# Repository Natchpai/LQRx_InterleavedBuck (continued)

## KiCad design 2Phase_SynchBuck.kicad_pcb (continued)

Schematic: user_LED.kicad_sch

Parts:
C801, C802: 100n; C_0402_nomDensity; Manufacturer Part Number GRM155R71H104KE14D
LD801, LD804: Orange; LED_0603_1608Metric; Manufacturer Part Numbe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 LTST-C190KFKT
LD802: Green; LED_0603_1608Metric; Manufacturer Part Numbe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 LTST-C191TGKT
LD803: Red; LED_0603_1608Metric; Manufacturer Part Numbe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 LTST-C191KRKT
Q801, Q802, Q803, Q804: GS2N7002KW; SOT-323_SC-70; Manufacturer Part Number GS2N7002KW
R801, R804: 499; R_0402_nomDensity; Manufacturer Part Number RC0402FR-07499RL
R802, R803: 1k; R_0402_nomDensity; Manufacturer Part Number RC0402FR-071KL
R805, R806, R807, R808: 100R; R_0402_nomDensity; Manufacturer Part Number RC0402FR-07100RL
R809, R810, R811, R812: 100k; R_0402_nomDensity; Manufacturer Part Number RC0402FR-07100KL

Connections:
+3V3: C801.1, C802.1, R801.1, R802.1, R803.1, R804.1; also elsewhere on the board
/Top/MCU IOs/LED_FAULT: R807.1, R811.1; also elsewhere on the board
/Top/MCU IOs/LED_IDLE: R805.1, R809.1; also elsewhere on the board
/Top/MCU IOs/LED_RUN: R806.1, R810.1; also elsewhere on the board
/Top/MCU IOs/LED_USER1: R808.1, R812.1; also elsewhere on the board
/Top/User LEDs/FLT_G: Q803.1 (G), R807.2
/Top/User LEDs/IDLE_G: Q801.1 (G), R805.2
/Top/User LEDs/LED_FLT_A: LD803.2 (A), R803.2
/Top/User LEDs/LED_FLT_K: LD803.1 (K), Q803.3 (D)
/Top/User LEDs/LED_IDLE_A: LD801.2 (A), R801.2
/Top/User LEDs/LED_IDLE_K: LD801.1 (K), Q801.3 (D)
/Top/User LEDs/LED_RUN_A: LD802.2 (A), R802.2
/Top/User LEDs/LED_RUN_K: LD802.1 (K), Q802.3 (D)
/Top/User LEDs/LED_USER1_A: LD804.2 (A), R804.2
/Top/User LEDs/LED_USER1_K: LD804.1 (K), Q804.3 (D)
/Top/User LEDs/RUN_G: Q802.1 (G), R806.2
/Top/User LEDs/USER1_G: Q804.1 (G), R808.2
GND: C801.2, C802.2, Q801.2 (S), Q802.2 (S), Q803.2 (S), Q804.2 (S), R809.2, R810.2, R811.2, R812.2; also elsewhere on the board

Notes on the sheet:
Status LEDs
15mcd @ 1.67mA
RUN
FALUT
USER
15mcd @ 0.67mA
Vf = 1.8V IV = 180mcd @20mA
User LEDs
Vf = 1.8V IV = 90mcd @20mA
Vf = 2.7V IV = 450mcd @20mA
IDLE
15mcd @ 3.3mA
[${#}] ${COMMENT1}

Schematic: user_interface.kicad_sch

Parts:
B901, B902: SW_Tactile_PTS815SJM250; Manufacturer Part Number PTS815SJM250SMTRLFS
C901, C902, C903: 100n; C_0402_nomDensity; Manufacturer Part Number GRM155R71H104KE14D
D901, D902, D903: ESD5Z3V3; D_SOD-523; Manufacturer Part Number ESD5Z3V3
R901, R904: 10k; R_0402_nomDensity; Manufacturer Part Number RC0402FR-1010KL
R902: 100R; R_0402_nomDensity; Manufacturer Part Number RC0402FR-07100RL
R903, R905: 1k; R_0402_nomDensity; Manufacturer Part Number RC0402FR-071KL
SW901: SW_SPDT; SW_SPDT_PCM12; Manufacturer Part Numbe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 SS-B90AP-W-SP2-S085

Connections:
+3V3: B901.1, B901.2, SW901.3 (C); also elsewhere on the board
/Top/MCU IOs/BT1_USER: C901.1, R903.2; also elsewhere on the board
/Top/MCU IOs/NRST: C902.1, R902.1; also elsewhere on the board
/Top/MCU IOs/SW1_USER: C903.1, R905.2; also elsewhere on the board
/Top/User Interface/BT1_USER_NODE: B901.3, B901.4, D901.1, R901.2, R903.1
/Top/User Interface/BT_RESET: B902.1, B902.2, D902.1, R902.2
/Top/User Interface/SW1_P1: R904.2, SW901.1 (A)
/Top/User Interface/SW1_POUT: D903.1, R905.1, SW901.2 (B)
GND: B902.3, B902.4, C901.2, C902.2, C903.2, D901.2, D902.2, D903.2, R901.1, R904.1; also elsewhere on the board

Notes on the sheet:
User Switch
[${#}] ${COMMENT1}
User Button
Reset Button
Place Diode close to the Button

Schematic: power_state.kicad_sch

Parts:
C101, C102, C110, C111, C112, C113, C122, C123, C124, C125: 4u7; C_1210_nomDensity; Manufacturer Part Number GRT32ER71H475KE01L
C103, C104, C105: 47u; CP_Elec_6.3x5.5_WCAP-ASLI; Manufacturer Part Number 865060543005
C106, C118: 4u7; C_0805_nomDensity; Manufacturer Part Number GRM21BZ7YA475KE15
C107, C108, C109, C114, C117, C119, C120, C121, C126, C129, C145: 100n; C_0402_nomDensity; Manufacturer Part Number GRM155R71H104KE14D
C115, C127: N/A; C_0402_nomDensity; not fitted
C116, C128: 100p; C_0402_nomDensity; Manufacturer Part Number GRM1555C1H101GA01D; not fitted
C130, C131, C132, C133, C134, C135, C137, C138, C139, C140, C141, C142: 4u7; C_1206_nomDesity; Manufacturer Part Number GRM31CR71H475KA12
C136, C143: 47u; CP_Elec_6.3x6_OS-CON-SVPK; Manufacturer Part Number 35SVPK47M
D101, D102, D103, D104: BAT54XV2T5G; D_SOD-523; Manufacturer Part Number BAT54XV2T5G
G101: SYM_Hot_Large; hot_surface
G102: SYM_ESD_Large; ESD-Logo_6.6x6mm_SilkScreen
G103: np_logo_5mm
L101: 1u; AMPLH5030S; Manufacturer Part Number AMPLH5030S-1R0MT
L102, L103: 10u; 744393665100; Manufacturer Part Number 744393665100
NT101: IN_SENSE+; NetTie-2_SMD_Pad0.15mm
NT102: IN_SENSE-; NetTie-2_SMD_Pad0.15mm
NT103, NT104: sw node; NetTie-2_SMD_Pad0.2mm
NT105: Vsense; NetTie-2_SMD_Pad0.2mm
Q101, Q103: BSZ018N04LS6; PG-TSDSON-8-26; Manufacturer Part Number BSZ018N04LS6ATMA1
Q102, Q104: IQE013N04LM6; PG-TSON-8-4; Manufacturer Part Number IQE013N04LM6ATMA1
R101: 5m; R_PA2512_R005-R006_YAGEO; Manufacturer Part Number PA2512FKE7W0R005E
R102, R103: 22R; R_0402_nomDensity; Manufacturer Part Number RC0402FR-1322RL
R104, R110: 21k5; R_0402_nomDensity; Manufacturer Part Number RC0402FR-0721K5L; not fitted
R105, R111: 100R; R_0402_nomDensity; Manufacturer Part Number RC0402FR-07100RL
R106, R112: 100k; R_0402_nomDensity; Manufacturer Part Number RC0402FR-07100KL
R107, R108, R113, R114: 2R21; R_0603_nomDensity; Manufacturer Part Numbe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 0603WAF221KT5E
R109, R115: N/A; R_0603_nomDensity; not fitted
R116, R118: 90k9; R_0603_nomDensity; Manufacturer Part Number RC0603FR-0790K9L
R117, R119: 10k; R_0603_nomDensity; Manufacturer Part Number RC0603FR-0710KL
TP101: Gate HS 1; TestPoint_Pad_D1.0mm_Bottom
TP102: Gate LS 1; TestPoint_Pad_D1.0mm_Bottom
TP103: Gate HS 2; TestPoint_Pad_D1.0mm_Bottom
TP104: Gate LS 2; TestPoint_Pad_D1.0mm_Bottom
TP105: Vin Filter; TestPoint_Pad_D1.0mm_Bottom
TP106: Switch-node 1; TestPoint_Pad_D1.0mm_Bottom
TP107: Switch-node 2; TestPoint_Pad_D1.0mm_Bottom
TP108: VREF1; TestPoint_Pad_D1.0mm_Bottom
TP109: VREF2; TestPoint_Pad_D1.0mm_Bottom
TP110: IL1; TestPoint_Pad_D1.0mm_Bottom
TP111: IL2; TestPoint_Pad_D1.0mm_Bottom
TP112: I_IN; TestPoint_Pad_D1.0mm_Bottom
TP113, TP114: GND; TestPoint_THTPad_1.0x1.0mm_Drill0.5mm
U101, U103: UCC27282DRC; 10-VSON(3x3)-DRC; Manufacturer Part Number UCC27282DRCT
U102, U104: ACS37030LLZATR-040B3; ACS37030LLZA; Manufacturer Part Number ACS37030LLZATR-040B3
U106: INA187A1IDBVR; SOT-23-6; Manufacturer Part Number INA187A1IDBVR

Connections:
+5V: R102.1; also elsewhere on the board
+9V: C106.1, C107.1, C118.1, C119.1, R104.2, R110.1, U101.1 (VDD), U103.1 (VDD); also elsewhere on the board
+S3V3: C117.1, C129.1, U102.6 (VDD), U104.6 (VDD); also elsewhere on the board
+VIN: C101.1, C102.1, C103.1, L101.1, NT102.2, R101.2, R118.1
/Top/MCU IOs/EN_CH1: R105.1, R106.1; also elsewhere on the board
/Top/MCU IOs/EN_CH2: R111.1, R112.1; also elsewhere on the board
/Top/MCU IOs/PWM_HS_CH1: U101.7 (HI); also elsewhere on the board
/Top/MCU IOs/PWM_HS_CH2: U103.7 (HI); also elsewhere on the board
/Top/MCU IOs/PWM_LS_CH1: U101.8 (LI); also elsewhere on the board
/Top/MCU IOs/PWM_LS_CH2: U103.8 (LI); also elsewhere on the board
/Top/Power Connectors/PWR_IN: NT101.2, R101.1; also elsewhere on the board
/Top/Power Connectors/PWR_OUT: C130.1, C131.1, C132.1, C133.1, C134.1, C135.1, C136.1, C137.1, C138.1, C139.1, C140.1, C141.1, C142.1, C143.1, NT105.1, U102.2 (IP-), U104.2 (IP-); also elsewhere on the board
/Top/Power State/DRV_GATE_HS1: D101.2 (A), Q101.4, R107.2, TP101.1 (1_1)
/Top/Power State/DRV_GATE_HS2: D103.2 (A), Q103.4, R113.2, TP103.1 (1_1)
/Top/Power State/DRV_GATE_LS1: D102.2 (A), Q102.4, R108.2, TP102.1 (1_1)
/Top/Power State/DRV_GATE_LS2: D104.2 (A), Q104.4, R114.2, TP104.1 (1_1)
/Top/Power State/DRV_HB1: C109.1, U101.3 (HB)
/Top/Power State/DRV_HB2: C121.1, U103.3 (HB)
/Top/Power State/DRV_HO1: D101.1 (K), R107.1, U101.4 (HO)
/Top/Power State/DRV_HO2: D103.1 (K), R113.1, U103.4 (HO)
/Top/Power State/DRV_HS1: C109.2, NT103.1, U101.5 (HS)
/Top/Power State/DRV_HS2: C121.2, NT104.1, U103.5 (HS)
/Top/Power State/DRV_LO1: D102.1 (K), R108.1, U101.10 (LO)
/Top/Power State/DRV_LO2: D104.1 (K), R114.1, U103.10 (LO)
/Top/Power State/EN1: C108.1, R104.1, R105.2, U101.6 (EN)
/Top/Power State/EN2: C120.1, R110.2, R111.2, U103.6 (EN)
/Top/Power State/I_INSE_VS: C145.1, R102.2, U106.6 (Vs)
/Top/Power State/I_IN_N: NT102.1, U106.4 (IN-)
/Top/Power State/I_IN_P: NT101.1, U106.3 (IN+)
/Top/Power State/I_IN_TR: R103.1, U106.1 (OUT)
/Top/Power State/PWR_SENSE_I_IN1: L102.2, U102.1 (IP+)
/Top/Power State/PWR_SENSE_I_IN2: L103.2, U104.1 (IP+)
/Top/Power State/PWR_SWNode_P1: C116.1, L102.1, NT103.2, Q101.1, Q102.8, R109.1, TP106.1 (1_1)
/Top/Power State/PWR_SWNode_P2: C128.1, L103.1, NT104.2, Q103.1, Q104.8, R115.1, TP107.1 (1_1)
/Top/Power State/SENSE_I_CH1: TP110.1 (1_1), U102.5 (VOUT); also elsewhere on the board
/Top/Power State/SENSE_I_CH2: TP111.1 (1_1), U104.5 (VOUT); also elsewhere on the board
/Top/Power State/SENSE_I_IN: R103.2, TP112.1 (1_1); also elsewhere on the board
/Top/Power State/SENSE_R_VOUT: NT105.2, R116.1
/Top/Power State/SENSE_VIN: R118.2, R119.1; also elsewhere on the board
/Top/Power State/SENSE_VOUT: R116.2, R117.1; also elsewhere on the board
/Top/Power State/SENSE_VREF1: TP108.1 (1_1), U102.4 (VREF)
/Top/Power State/SENSE_VREF2: TP109.1 (1_1), U104.4 (VREF)
GND: C101.2, C102.2, C103.2, C104.2, C105.2, C106.2, C107.2, C108.2, C110.2, C111.2, C112.2, C113.2, C114.2, C115.2, C116.2, C117.2, C118.2, C119.2, C120.2, C122.2, C123.2, C124.2, C125.2, C126.2, C127.2, C128.2, C129.2, C130.2, C131.2, C132.2, C133.2, C134.2, C135.2, C136.2, C137.2, C138.2, C139.2, C140.2, C141.2, C142.2, C143.2, C145.2, Q102.1, Q104.1, R106.2, R112.2, R117.2, R119.2, TP113.1 (1_1), TP114.1 (1_1), U101.9 (VSS), U101.11 (VSS), U102.3 (GND), U103.9 (VSS), U103.11 (VSS), U104.3 (GND), U106.2 (GND), U106.5 (REF); also elsewhere on the board
unnamed: C115.1, R109.2
unnamed: C127.1, R115.2
PWR_VIN_FILT: C104.1, C105.1, C110.1, C111.1, C112.1, C113.1, C114.1, C122.1, C123.1, C124.1, C125.1, C126.1, L101.2, Q101.8, Q103.8, TP105.1 (1_1)

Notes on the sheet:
Ø6.3mm
R_{G}= 0R9
Current Sensor
ESD Sensitive
10:1
Place C104 and C105 near phase 1 and phase 2, respectively.
GRT32ER71H475KE01L
Hot surface
For Output Cap.
PHASE 1
-33%
Output Capacitor 4.7uFx12 Derating -15.6% @12VDC = 47.6uF
[${#}] ${COMMENT1}
GRT32ER71H475KE01 (Murata MLCC 4u7 50V) DC-Bias vs Capacitance Derating
±1%
±3%
GRT32ER71H475KE01
R_{T} = 9 x R_{B}
A1's GAIN: 20V/V I = 1/20 x Vout/0.005
10A
24V
Output Voltage Sense
Input Filter
GRM31CR71H475KA12 (Murata MLCC 4u7 50V) Capacitance Derating vs DC-Bias
C_{snub} = (4~8) C_{par}
R_{snub} = 1/Q [ sqrt( L_{par} / C_{snub} ) ]
R_{G}= 1R3
I_{IN} Sense
-15.6%
Input Voltage Sense
15m DCR
NP LOGO 5mm
GRM31CR71H475KA12
5m6 DCR
L_{par} = 1 / [ 2pi f_{1} C_{par} ]
Z_{Filter Out} Peak -13.78dB @28kHz <Atten. -20.5dB @ 200kHz
PHASE 2
Test Point
Total ESR 0.196 ohm
12V

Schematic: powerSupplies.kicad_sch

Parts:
C301, C303, C310, C312: 4u7; C_1210_nomDensity; Manufacturer Part Number GRT32ER71H475KE01L
C302, C311: 22u; CP_Elec_5x5.5_WCAP-ASLI; Manufacturer Part Number 865080542006
C304, C305, C306, C313, C314, C315, C320, C323, C325, C328, C329: 100n; C_0402_nomDensity; Manufacturer Part Number GRM155R71H104KE14D
C307, C308, C309, C316, C317, C318: 4u7; C_0805_nomDensity; Manufacturer Part Number GRM21BZ7YA475KE15
C319, C321, C322, C324, C326, C327: 2u2; C_0603_nomDensity; Manufacturer Part Number GRM188Z71C225KE43
D301: BAT60JFILM; D_SOD-323; Manufacturer Part Number BAT60JFILM; not fitted
L301, L303: 2u2; L_0806_BDCD00201610; Manufacturer Part Number BDCD002016102R2MS1
L302, L304: 22u; AMDLA4020S; Manufacturer Part Number AMDLA4020S-220MT
LD301: Green; LED_0603_1608Metric; Manufacturer Part Numbe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 LTST-C191TGKT
NT303, NT304, NT305: EN; NetTie-2_SMD_Pad0.15mm
R301, R302: 20m; R_PA1206_R004-R020_YAGEO; Manufacturer Part Number PA1206FRE070R02Z
R303: 162k; R_0402_nomDensity; Manufacturer Part Number RC0402FR-07162KL
R304, R306, R308, R310: 21k5; R_0402_nomDensity; Manufacturer Part Number RC0402FR-0721K5L
R305: 221k; R_0402_nomDensity; Manufacturer Part Number RC0402FR-07221KL
R307: 110k; R_0402_nomDensity; Manufacturer Part Number RC0402FR-07110KL
R309: 118k; R_0402_nomDensity; Manufacturer Part Number RC0402FR-07118KL
R311, R313: 0R; R_0603_nomDensity; Manufacturer Part Number RC0603JR-070RL
R312: 5k11; R_0402_nomDensity; Manufacturer Part Number RC0402FR-135K11L
TP301: +9V; TestPoint_NoSlik_D1.0mm_Top
TP302: +5V; TestPoint_NoSlik_D1.0mm_Top
TP303: +USB; TestPoint_NoSlik_D1.0mm_Bottom
TP304: +3V3; TestPoint_NoSlik_D1.0mm_Top
TP305: +A3V3; TestPoint_NoSlik_D1.0mm_Bottom
TP306: +S3V3; TestPoint_NoSlik_D1.0mm_Bottom
TP307: GND; TestPoint_THTPad_1.0x1.0mm_Drill0.5mm
U301, U302: LMR54410DBVR; SOT-23-6; Manufacturer Part Number LMR54410DBVR
U303, U304: SPX3819M5-L-3-3/TR; SOT-23-5; Manufacturer Part Number SPX3819M5-L-3-3/TR
U305: LDLN025M33R; SOT-23-5; Manufacturer Part Number LDLN025M33R
U306: LM66100DCK; DCK0006A_TI; Manufacturer Part Number LM66100DCK

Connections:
+3V3: C321.1, TP304.1 (1_1), U303.5 (OUT); also elsewhere on the board
+5V: C315.1, C316.1, C317.1, C318.1, C319.1, C322.1, C325.1, L304.2, NT303.1, NT304.1, R309.1, R311.1, R312.1, R313.2, TP302.1 (1_1), U303.1 (IN), U304.1 (IN); also elsewhere on the board
+9V: C306.1, C307.1, C308.1, C309.1, L302.2, R305.1, TP301.1 (1_1); also elsewhere on the board
+A3V3: C327.1, TP305.1 (1_1), U305.5 (OUT); also elsewhere on the board
+S3V3: C324.1, TP306.1 (1_1), U304.5 (OUT); also elsewhere on the board
+VUSB: C328.1, D301.2 (A), TP303.1 (1_1), U306.1 (VIN); also elsewhere on the board
/Top/Power Connectors/PWR_IN: R301.1, R302.1; also elsewhere on the board
/Top/Power Supplies/5V_SW: C314.2, L304.1, U302.6 (SW)
/Top/Power Supplies/5V_VIN: C310.1, L303.1, R302.2
/Top/Power Supplies/5V_VIN__FILT: C311.1, C312.1, C313.1, L303.2, R307.1, U302.5 (VIN)
/Top/Power Supplies/9V_SW: C305.2, L302.1, U301.6 (SW)
/Top/Power Supplies/9V_VIN: C301.1, L301.1, R301.2
/Top/Power Supplies/9V_VIN__FILT: C302.1, C303.1, C304.1, L301.2, R303.1, U301.5 (VIN)
/Top/Power Supplies/+5VUSB: C329.1, D301.1 (K), R313.1, U306.3 (~CE), U306.6 (VOUT)
/Top/Power Supplies/A3V3_IN: C326.1, NT305.1, R311.2, U305.1 (IN)
/Top/Power Supplies/BP_3V3: C320.1, U303.4 (BP)
/Top/Power Supplies/BP_3V3_S: C323.1, U304.4 (BP)
/Top/Power Supplies/BUS_LED_A: LD301.2 (A), R312.2
/Top/Power Supplies/CB_5V: C314.1, U302.1 (CB)
/Top/Power Supplies/CB_9V: C305.1, U301.1 (CB)
/Top/Power Supplies/EN_3V3: NT303.2, U303.3 (EN)
/Top/Power Supplies/EN_3V3_S: NT304.2, U304.3 (EN)
/Top/Power Supplies/EN_5V: R307.2, R308.1, U302.4 (EN)
/Top/Power Supplies/EN_9V: R303.2, R304.1, U301.4 (EN)
/Top/Power Supplies/EN_A3V3: NT305.2, U305.3 (EN)
/Top/Power Supplies/FB_5V: R309.2, R310.1, U302.3 (FB)
/Top/Power Supplies/FB_9V: R305.2, R306.1, U301.3 (FB)
GND: C301.2, C302.2, C303.2, C304.2, C306.2, C307.2, C308.2, C309.2, C310.2, C311.2, C312.2, C313.2, C315.2, C316.2, C317.2, C318.2, C319.2, C320.2, C321.2, C322.2, C323.2, C324.2, C325.2, C326.2, C327.2, C328.2, C329.2, LD301.1 (K), R304.2, R306.2, R308.2, R310.2, TP307.1 (1_1), U301.2 (GND), U302.2 (GND), U303.2 (GND), U304.2 (GND), U305.2 (GND), U306.2 (GND); also elsewhere on the board

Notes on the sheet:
[${#}] ${COMMENT1}
STpin Open-Drain EN :HI-Z DIS :LOW
LDO 3V3 500mA (Digital path)
LDO 3V3 500mA (Sensor path)
R_{p} = Z_{0}^{2} / DCR
R_{d} = 0.71Ohm, Q=0.7
On Page 1
Z_{Filter Out}Peak -2dB @63.3kHz <Atten. -48.4dB @ 1MHz
R_{p} = 0.84^{2} / 0.2 = 3.528
LDO 3V3 250mA (Analog path)
Reverse Current Blocking
LED Indicators
R_{d} = Z_{0}^{2} / ( Z_{0}/Q - DCR )
*Enable when V_{IN} is above 11V
R_{total} = R_{p} // R_{d}
R_{Eq}Parallel of DCR @ f_{0}
EN: +VUSB > +5V
Q = R_{total} / Z_{0}
Buck Converter 5V 1A (1.1MHz)
10mcd @ 0.5mA
0.2DCR
PWR
Test Point
*Enable when V_{IN} is above 7V
Vf = 2.7V
Buck Converter 9V 1A (1.1MHz)
Determine R_{d} = 1.1Ohm, Q=1
Output Capacitor C_{OUT} > 0.5 x (8 x I)/(f x DeltaVo) > 0.5x(8x0.6)/(1.1Meg x 0.2) C_{OUT} > 11uF , Transient Load (0.6A) Derated -44% @9V = 2.79uF 3x3.79 = 8.37uF
DESIGN NOTE: C_{d}=5*C=18uF Z_{0} = sqrt(L/C) =sqrt(2.2/3.1)=0.84ohm
DESIGN NOTE: The EN rising threshold is 1.23V The EN falling threshold is 1.1V When V_{EN} pin is below 0.95V(min) the device is in shutdown mode.
R_{ENT}=((V/1.23)-1) x R_{ENB} =((10.5/1.23)-1) x 21.5k = 162.03k => 162k Ohm EN = ((21.5+162)/21.5)x1.23 = 10.49V DIS = ((21.5+162)/21.5)x1.1 = 9.38V
Derated -19.1% @5V = 4.03uF 3x4.03u = 12uF
Feeback Resistor R_{FBT} = ((V_{OUT}-V_{REF})/ V_{REF}) x R_{FBB} = ((9 - 0.8)/ 0.8) x 22.5k = ~220.3k Ohm V_{OUT} = V_{REF} x (1 + R_{FBT}/R_{FBB}) = 0.8 x (1 + (221/22.5)) = 9.023V
Feedback Resistot R_{FBT} = ((V_{OUT}-V_{REF})/ V_{REF}) x R_{FBB} = ((5 - 0.8)/ 0.8) x 21.5k = 116k Ohm V_{OUT} = V_{REF} x (1 + R_{FBT}/R_{FBB}) = 0.8 x (1 + (118/22.5)) = 5.19V
<Target 18uF ESR 1.1ohm> Used E.CAP(22uF, ESR 1ohm) x1 for stability
LAYOUT NOTE: Place this power supply near the current sensor
R_{ENT}=((V/1.23)-1) x R_{ENB} =((7/1.23)-1) x 21.5k = 100.8k => 100k Ohm EN = ((21.5+100)/21.5)x1.23 = 6.95V DIS = ((21.5+100)/21.5)x1.1 = 6.27V
Derated -13.7% @3V3 = 1.98uF

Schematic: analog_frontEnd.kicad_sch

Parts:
C601, C602, C603, C604, C605: 1n; C_0402_nomDensity; Manufacturer Part Number GRM1555C1H102JA01D
C606, C607: 100n; C_0402_nomDensity; Manufacturer Part Number GRM155R71H104KE14D
R601, R602, R603, R605: 49R9; R_0402_nomDensity; Manufacturer Part Number RC0402FR-1349R9L
R604: 100R; R_0402_nomDensity; Manufacturer Part Number RC0402FR-07100RL
TP601: Analog Vout; TestPoint_NoSlik_D0.5mm_Top
TP602: Analog VIN; TestPoint_NoSlik_D0.5mm_Bottom
TP603: GND; TestPoint_NoSlik_D0.5mm_Top
TP604: GND; TestPoint_NoSlik_D0.5mm_Bottom
U601, U602: TLV9061IDBVR; SOT-23-5; Manufacturer Part Number TLV9061IDBVR

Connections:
+A3V3: C606.1, C607.2, U601.5 (V+), U602.5 (V+); also elsewhere on the board
/Top/Analog Front-End/OP_FB_VIN: R605.1, U602.1, U602.4 (-)
/Top/Analog Front-End/OP_FB_VO: R603.1, U601.1, U601.4 (-)
/Top/MCU IOs/ADC1_I_CH1: C601.1, R601.2; also elsewhere on the board
/Top/MCU IOs/ADC2_I_CH2: C602.1, R602.2; also elsewhere on the board
/Top/MCU IOs/ADC3_VOUT: C603.1, R603.2, TP601.1 (1_1); also elsewhere on the board
/Top/MCU IOs/ADC4_I_IN: C604.1, R604.2; also elsewhere on the board
/Top/MCU IOs/ADC4_VIN: C605.1, R605.2, TP602.1 (1_1); also elsewhere on the board
/Top/Power State/SENSE_I_CH1: R601.1; also elsewhere on the board
/Top/Power State/SENSE_I_CH2: R602.1; also elsewhere on the board
/Top/Power State/SENSE_I_IN: R604.1; also elsewhere on the board
/Top/Power State/SENSE_VIN: U602.3 (+); also elsewhere on the board
/Top/Power State/SENSE_VOUT: U601.3 (+); also elsewhere on the board
GND: C601.2, C602.2, C603.2, C604.2, C605.2, C606.2, C607.1, TP603.1 (1_1), TP604.1 (1_1), U601.2 (V-), U602.2 (V-); also elsewhere on the board

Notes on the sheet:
ADC1, 2 (48.571429MHz) 12-Bit Res.
R_{AIN (MAX)} = 39k
Input Current Path (Low Speed)
R_{AIN (MAX)} = 100R
t_{ACQ} = 2.5 Cycle = 58.8ns
Z_{sense} = 9kOhm
t_{ACQ} = 640.5 Cycle = 15.07us
t_{settling} = ~450ns
[${#}] ${COMMENT1}
C_{ADC} = 10pF
ADC4 (42.5MHz) 12-Bit Res.
t_{ACQ} = 2.5 Cycle = 51.47ns
Output Voltage Path (High Speed)
Current Path (High Speed)
, Error < 0.02%
Input Voltage Path (Low Speed)
ADC3 (42.5MHz) 12-Bit Res.
t_{settling} = ~9 x RC
t_{settling} = ~1us
LAYOUT NOTE: Placing OpAmp and RC Filter close to the ADC input or Analog Zone
LAYOUT NOTE: Rount away from magnetic compenents

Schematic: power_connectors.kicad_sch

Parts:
C201: 1u; C_0805_nomDensity; Manufacturer Part Numbe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 CL21B105KBFNNNE
CN201, CN202, CN203, CN204: 04A2; Molex_Mini-Fit_Jr_5569-04A2_2x02_P4.20mm_Horizontal; Manufacturer Part Number 10127819-04211LF
CN205: SMA-J-P-H-ST-EM1; SMA_Samtec_SMA-J-P-H-ST-EM1_EdgeMount
D201, D202: SMF4L28A; D_SOD-123FL; Manufacturer Part Number SMF4L28A
R201: 1k; R_1206_YEGEO; Manufacturer Part Number AC1206FR-7W1KL
R202: 49R9; R_0402_nomDensity; Manufacturer Part Number RC0402FR-1349R9L

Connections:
/Top/Power Connectors/CP_C_R: C201.2, R202.2
/Top/Power Connectors/CP_R_SMA: CN205.1 (In), R202.1
/Top/Power Connectors/PWR_IN: CN201.3, CN201.4, CN202.3, CN202.4, D201.1; also elsewhere on the board
/Top/Power Connectors/PWR_OUT: C201.1, CN203.3, CN203.4, CN204.3, CN204.4, D202.1, R201.1; also elsewhere on the board
GND: CN201.1, CN201.2, CN202.1, CN202.2, CN203.1, CN203.2, CN204.1, CN204.2, CN205.2 (Ext), D201.2, D202.2, R201.2; also elsewhere on the board

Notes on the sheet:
x2 Probe
[${#}] ${COMMENT1}
30V 20A MAX
10127819-04211LF
Input Connector
For Ripple Measurement
Molex Mini-Fit Jr 5569-04A2 or equivalent.
30V 20A MAX
Output Connector
Output AC Coupling
Place TVS Diode close the Connector

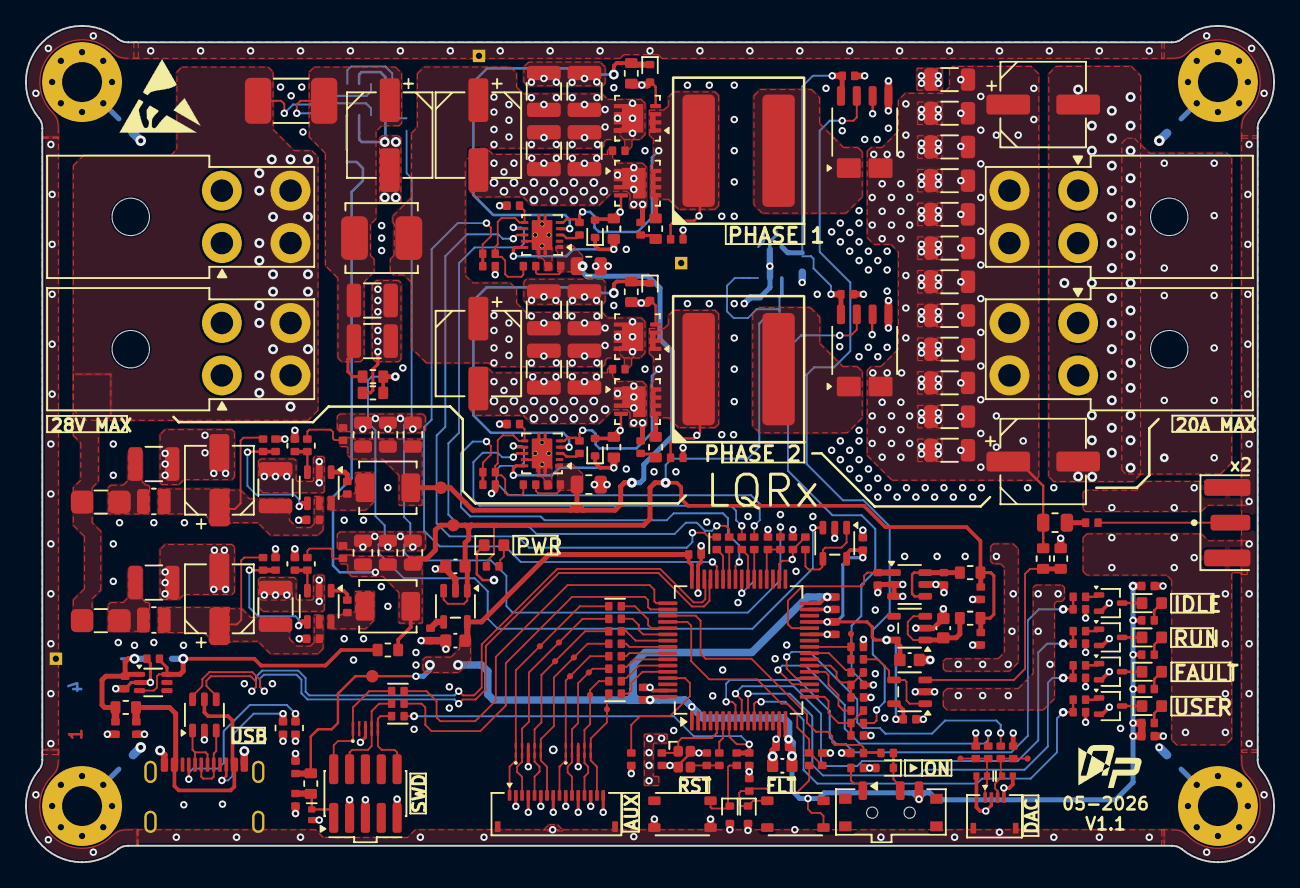
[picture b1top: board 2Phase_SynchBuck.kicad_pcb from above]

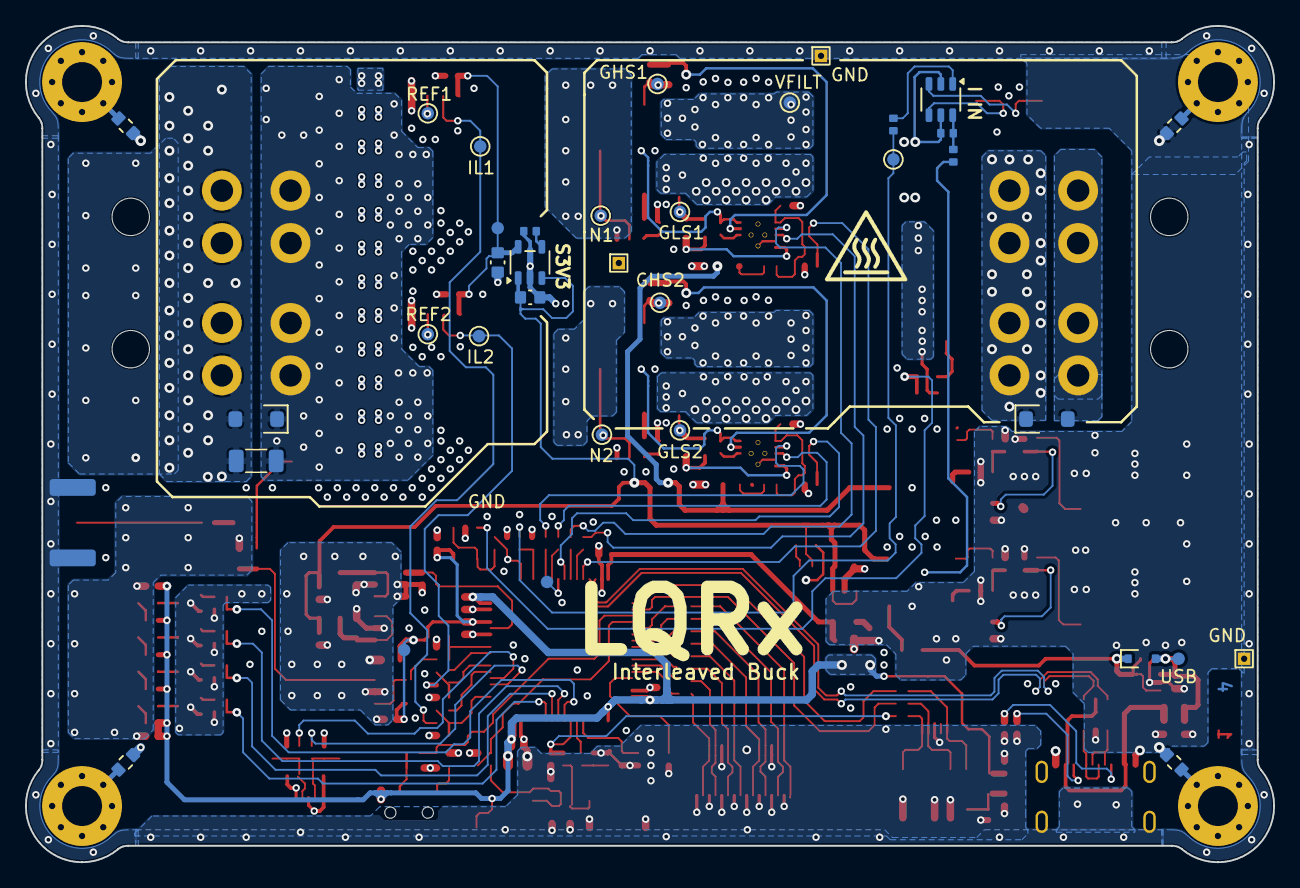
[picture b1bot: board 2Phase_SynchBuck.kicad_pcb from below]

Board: 4 copper layers, 100.0 x 67.0 mm, 305 parts (41 on the bottom side), 152 nets.

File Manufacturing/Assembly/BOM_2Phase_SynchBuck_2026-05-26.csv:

Reference,Qty,Value,Manufacturer Name,Manufacturer Part Number,Supplier Part Number
"B901,B902",10,SW_Tactile_PTS815SJM250,C&K,PTS815SJM250SMTRLFS,CKN12215-1-ND
"C101,C102,C110,C111,C112,C113,C122,C123,C124,C125,C301,C303,C310,C312",30,4u7,Murata,GRT32ER71H475KE01L,490-GRT32ER71H475KE01LCT-ND
"C103,C104,C105",10,47u,Würth Elektronik,8.65061E+11,732-8585-1-ND
"C106,C118,C307,C308,C309,C316,C317,C318",50,4u7,Murata,GRM21BZ7YA475KE15,490-GRM21BZ7YA475KE15LCT-ND
"C107,C108,C109,C114,C117,C119,C120,C121,C126,C129,C145,C304,C305,C306,C313,C314,C315,C320,C323,C325,C328,C329,C402,C403,C404,C405,C406,C407,C408,C409,C606,C607,C701,C702,C703,C704,C801,C802,C901,C902,C903",50,100n,Murata,GRM155R71H104KE14D,490-10700-1-ND
"C116,C128",10,100p,Murata,GRM1555C1H101GA01D,490-6188-1-ND
"C130,C131,C132,C133,C134,C135,C137,C138,C139,C140,C141,C142",25,4u7,Murata,GRM31CR71H475KA12,490-6521-1-ND
"C136,C143",5,47u,Panasonic,35SVPK47M,P122127CT-ND
"C302,C311",10,22u,Würth Elektronik,8.65081E+11,732-8505-1-ND
"C319,C321,C322,C324,C326,C327,C401",10,2u2,Murata,GRM188Z71C225KE43,490-GRM188Z71C225KE43JCT-ND
"C501,C502",10,6p8,Murata,GCM1555C1H6R8FA16D,490-GCM1555C1H6R8FA16DCT-ND
"C601,C602,C603,C605",10,47p,Murata,GRM1555C1H470GA01D,490-8206-1-ND
C604,10,1n,Murata,GRM1555C1H102JA01D,490-3244-1-ND
"CN201,CN202,CN203,CN204",10,04A2,Amphenol ICC,10127819-04211LF,609-4867-ND
CN701,5,USB4215-03-A,GCT,USB4215-03-A,2073-USB4215-03-ACT-ND
CN702,2,Conn_JTAG_STDC10,GCT,BD125-10-A-0305-0580-L-B,2073-BD125-10-A-0305-0580-L-BCT-ND
CN703,2,FFC2B28-16-G,GCT,FFC2B28-16-G,2073-FFC2B28-16-GCT-ND
CN704,2,FFC2B28-04-G,GCT,FFC2B28-04-G,2073-FFC2B28-04-GCT-ND
"D101,D102,D103,D104",10,BAT54XV2T5G,onsemi,BAT54XV2T5G,BAT54XV2T5GOSCT-ND
"D201,D202",5,SMF4L28A,Littelfuse Inc.,SMF4L28A,F7483CT-ND
D301,10,BAT60JFILM,STMicroelectronics,BAT60JFILM,497-3707-1-ND
"D701,D705,D706",10,SP3031-01ETG,Littelfuse Inc.,SP3031-01ETG,F5769CT-ND
"D702,D703,D704",10,PUSB3FR4Z,Nexperia,PUSB3FR4Z,1727-2026-1-ND
L101,5,1u,Abracon LLC,AMPLH5030S-1R0MT,535-AMPLH5030S-1R0MTCT-ND
"L102,L103",4,10u,Würth Elektronik,7.44394E+11,732-744393665100CT-ND
"L301,L303",5,2u2,Pulse Electronics,BDCD002016102R2MS1,553-BDCD002016102R2MS1CT-ND
"L302,L304",5,22u,Abracon LLC,AMDLA4020S-220MT,535-AMDLA4020S-220MTCT-ND
"Q101,Q103",5,BSZ018N04LS6,Infineon Technologies,BSZ018N04LS6ATMA1,448-BSZ018N04LS6ATMA1CT-ND
"Q102,Q104",5,IQE013N04LM6,Infineon Technologies,IQE013N04LM6ATMA1,448-IQE013N04LM6ATMA1CT-ND
"Q105,Q106,Q801,Q802,Q803,Q804",25,GS2N7002KW,Good-Ark,GS2N7002KW,4786-GS2N7002KWCT-ND
R101,2,5m,YAGEO,PA2512FKE7W0R005E,YAG6091CT-ND
"R102,R103,R501,R503,R504,R505,R506,R705,R706,R707,R708,R709,R710,R711,R712,R713,R714,R715,R716,R717",100,22R,YAGEO,RC0402FR-1322RL,13-RC0402FR-1322RLCT-ND
"R104,R110,R304,R306,R308,R310",25,21k5,YAGEO,RC0402FR-0721K5L,311-21.5KLRCT-ND
"R105,R111,R604,R805,R806,R807,R808,R902",25,100R,YAGEO,RC0402FR-07100RL,311-100LRCT-ND
"R106,R112,R809,R810,R811,R812",25,100k,YAGEO,RC0402FR-07100KL,311-100KLRCT-ND
"R116,R118",50,90k9,YAGEO,RC0603FR-0790K9L,311-90.9KHRCT-ND
"R117,R119",50,10k,YAGEO,RC0603FR-0710KL,311-10.0KHRCT-ND
R201,10,1k,YAGEO,AC1206FR-7W1KL,13-AC1206FR-7W1KLCT-ND
"R202,R507,R508,R601,R602,R603,R605",25,49R9,YAGEO,RC0402FR-1349R9L,13-RC0402FR-1349R9LCT-ND
"R301,R302",10,20m,YAGEO,PA1206FRE070R02Z,13-PA1206FRE070R02ZCT-ND
R303,10,162k,YAGEO,RC0402FR-07162KL,YAG2370CT-ND
R305,10,221k,YAGEO,RC0402FR-07221KL,YAG3059CT-ND
R307,10,110k,YAGEO,RC0402FR-07110KL,311-110KLRCT-ND
R309,10,118k,YAGEO,RC0402FR-07118KL,YAG2369CT-ND
"R311,R313,R401,R701,R704,R718,R719,R720,R721",100,0R,YAGEO,RC0603JR-070RL,311-0.0GRCT-ND
"R312,R702,R703",100,5k11,YAGEO,RC0402FR-135K11L,13-RC0402FR-135K11LCT-ND
"R502,R802,R803,R903,R905",100,1k,YAGEO,RC0402FR-071KL,311-1.00KLRCT-ND
"R801,R804",100,499,YAGEO,RC0402FR-07499RL,311-499LRCT-ND
"R901,R904",100,10k,YAGEO,RC0402FR-1010KL,13-RC0402FR-1010KLCT-ND
"U101,U103",5,UCC27282DRC,Texas Instruments,UCC27282DRCT,296-53422-1-ND
"U102,U104",5,ACS37030LLZATR-040B3,Allegro MicroSystems,ACS37030LLZATR-040B3,620-ACS37030LLZATR-040B3CT-ND
U106,2,INA187A1IDBVR,Texas Instruments,INA187A1IDBVR,296-INA187A1IDBVRCT-ND
"U301,U302",10,LMR54410DBVR,Texas Instruments,LMR54410DBVR,296-LMR54410DBVRCT-ND
"U303,U304",10,SPX3819M5-L-3-3/TR,MaxLinear,SPX3819M5-L-3-3/TR,1016-1873-1-ND
U305,10,LDLN025M33R,STMicroelectronics,LDLN025M33R,497-17777-1-ND
U306,2,LM66100DCK,Texas Instruments,LM66100DCK,296-53540-1-ND
U401,2,STM32G474RET6,STMicroelectronics,STM32G474RET6,497-STM32G474RET6-ND
U402,3,MCP1501T-30E,Microchip Technology,MCP1501T-30E,MCP1501T-30E/CHYCT-ND
"U601,U602",10,TLV9061SIDBVR,Texas Instruments,TLV9061SIDBVR,296-53200-1-ND
U701,10,USBLC6-2SC6,STMicroelectronics,USBLC6-2SC6,497-5235-1-ND
X501,10,ABM11W-24MHz-8,Abracon LLC,ABM11W-24.0000MHZ-8-B1U-T3,535-13834-1-ND

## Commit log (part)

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2026-05-27 Added Library
2026-05-27 Added Image, logo
2026-05-27 Added Kicad templates
2026-05-27 Added LTSpice Files
2026-05-27 Added Schematic Files
2026-05-27 Added Design Rules
2026-05-27 Added board2pdf configs
2026-05-27 Added Project file
2026-05-27 Added PCB files
2026-05-27 Added sch_data.json
2026-05-27 Added FB and Sym tables
2026-05-29 Render PCB v1.0 Top and BOT View
2026-05-29 Modified part number
    Added 2nd Supplier
    Added 2nd Mfr, Mfr NO.
2026-05-29 Create BOM_2Phase_SynchBuck_v1.0_2026-05-29.csv
    Export BOM v1.0 2026-05-29
2026-05-29 Deleted unuse templates files
2026-05-29 Updated templates
2026-05-29 Updated template in sch
2026-06-03 Updated Schematic v1.0
2026-06-03 Create LQRx_2PBuck-V1-Gerber-03062026.zip
    Released PC Board v1.0
2026-06-03 Rename schematic file
2026-06-03 Initialize README with some project details
    Added project overview, specifications, but NO features to README.
2026-06-07 Update 2Phase_SynchBuck.kicad_pcb
    Restored outer via annular ring
2026-06-12 Enhance README with features and specifications
    Updated README.md to include key features, specifications, and control implementation details for the Digitally Controlled Interleaved Buck Converter.
2026-06-28 Rev1.1
    - Removed the Mosfet that Enable the ICs Gate Driver (p.1)
    - Changed ADC input Capacitor 47pF to 1nF. (p.6
2026-06-28 Update 2Phase_SynchBuck.kicad_pro
    Changed Date
